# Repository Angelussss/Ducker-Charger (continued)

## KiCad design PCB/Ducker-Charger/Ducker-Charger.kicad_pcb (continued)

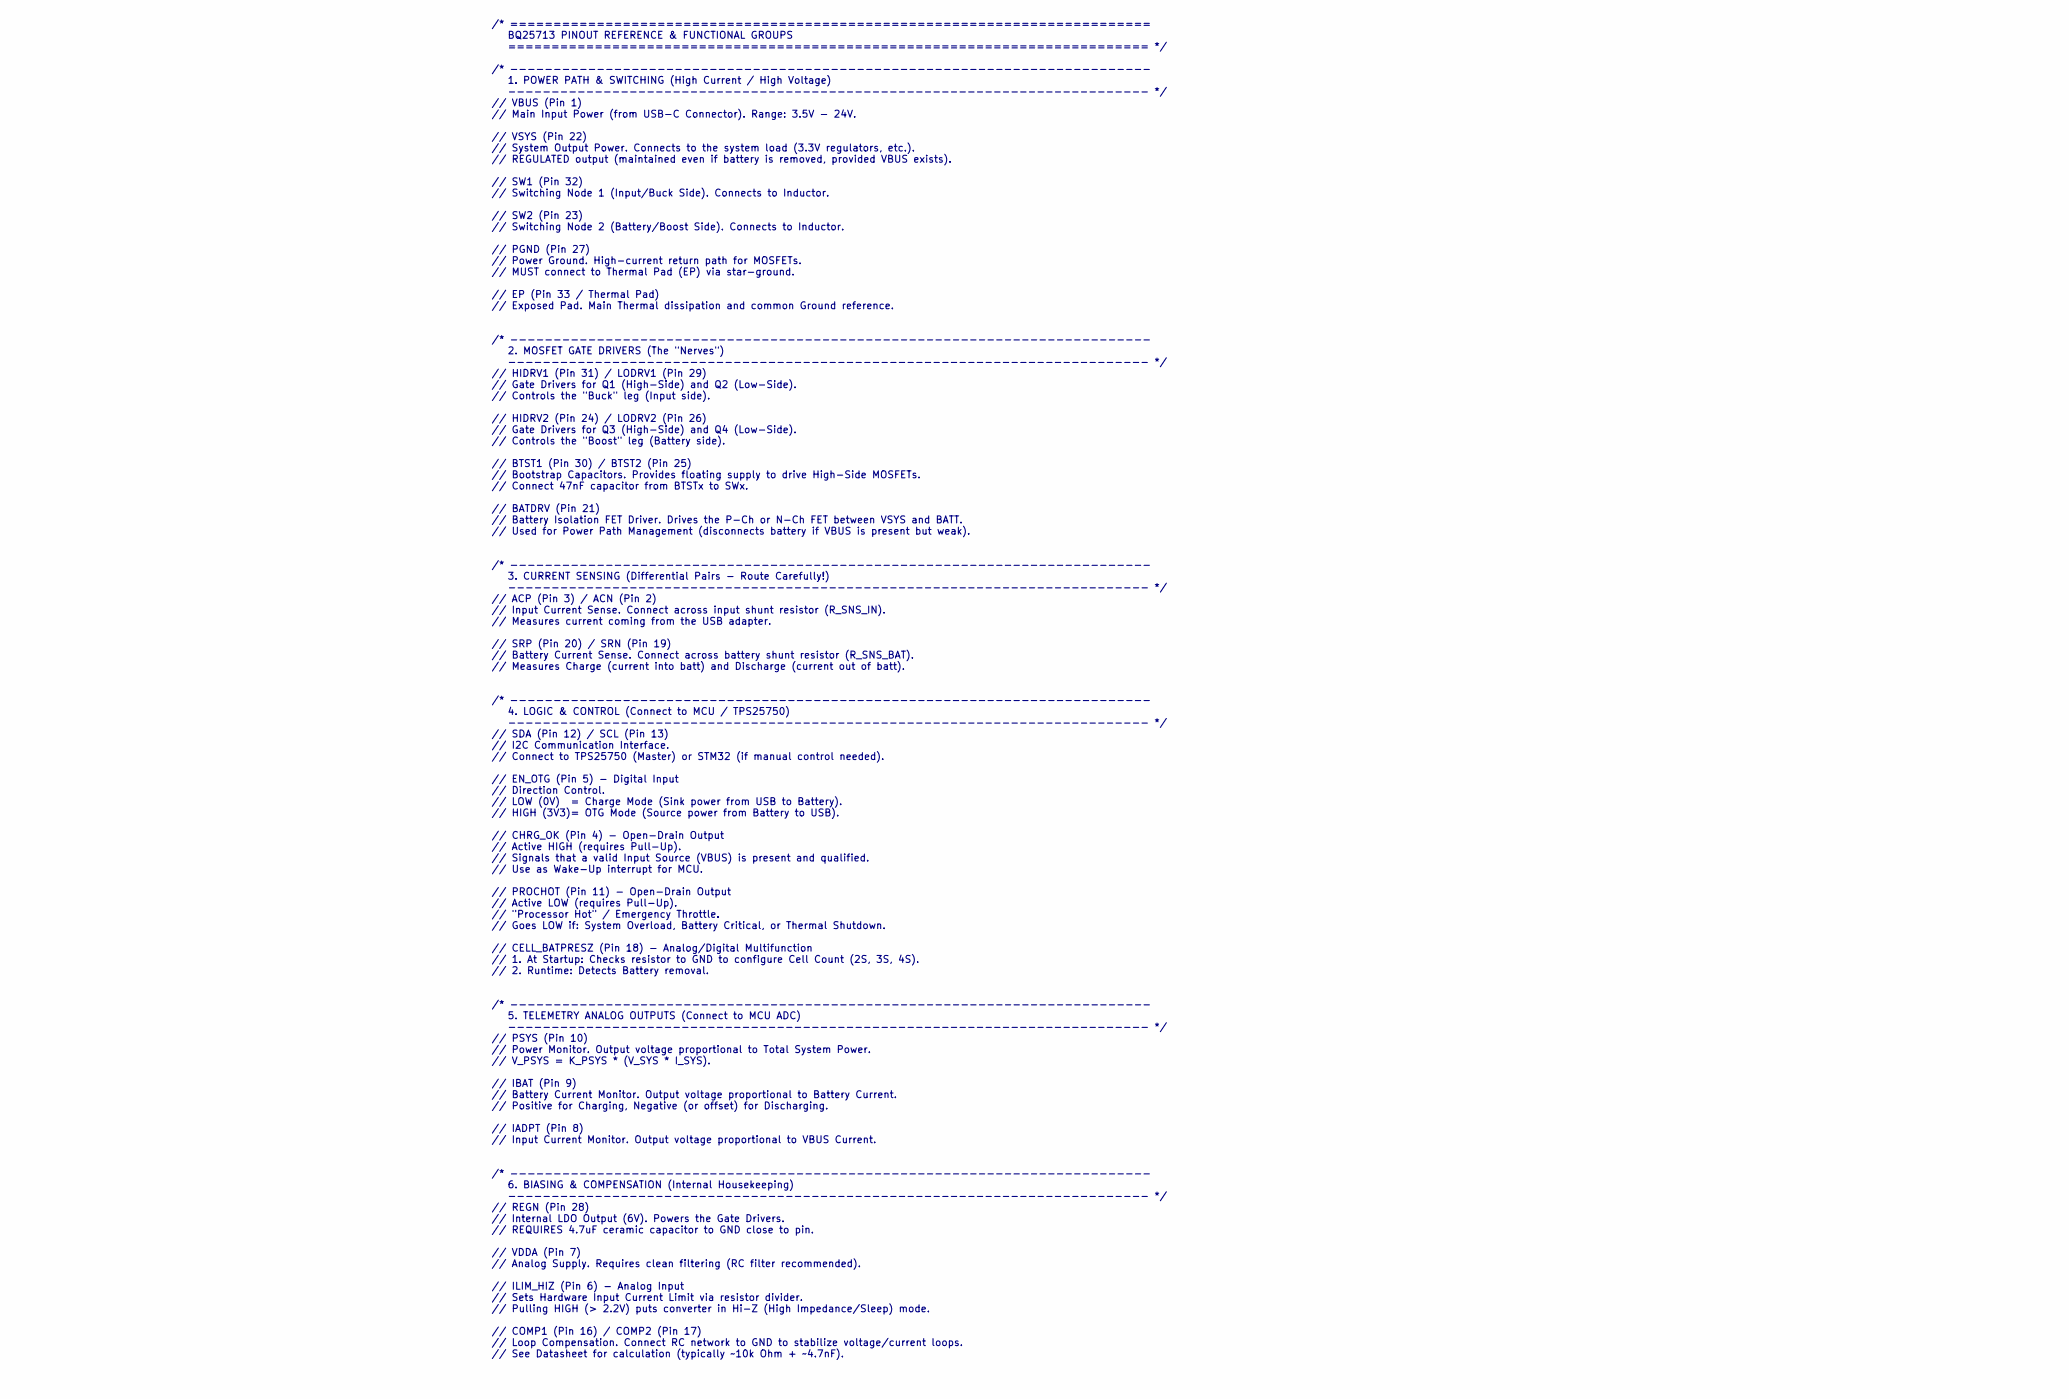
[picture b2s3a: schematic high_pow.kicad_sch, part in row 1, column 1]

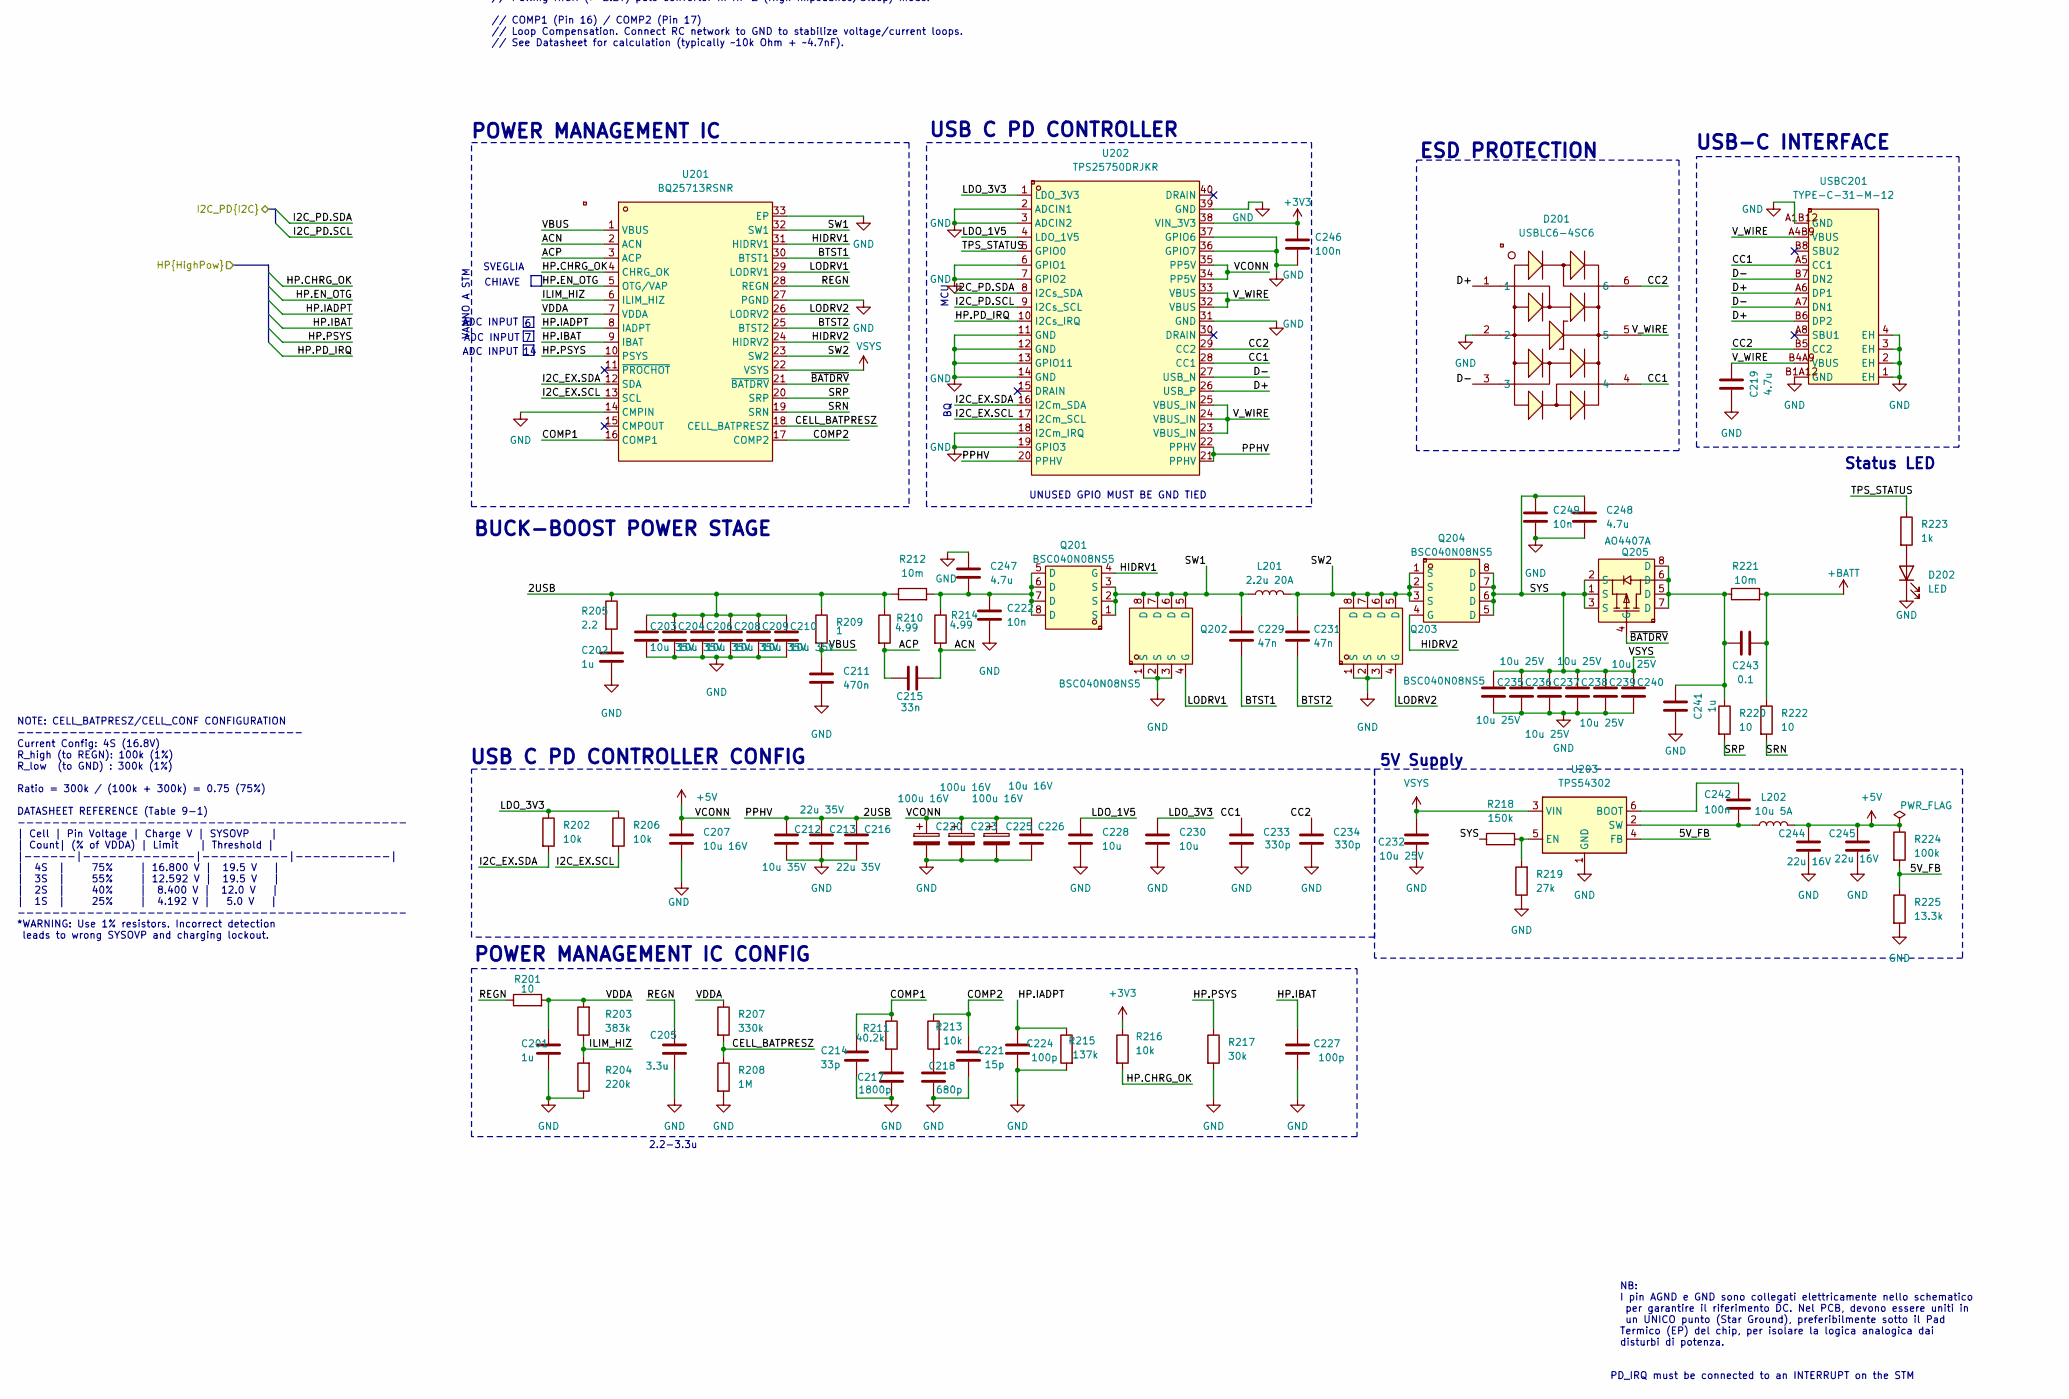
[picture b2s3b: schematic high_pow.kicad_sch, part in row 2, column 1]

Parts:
C201, C202, C241: 1u; C_0805_2012Metric
C203, C204, C206, C208, C209, C210, C212: 10u 35V; C_1206_3216Metric
C205: 3.3u; C_0805_2012Metric
C207, C226: 10u 16V; C_0603_1608Metric
C211: 470n; C_0805_2012Metric
C213, C216: 22u 35V; C_1210_3225Metric
C214: 33p; C_0603_1608Metric
C215: 33n; C_0603_1608Metric
C217: 1800p; C_0603_1608Metric
C218: 680p; C_0603_1608Metric
C219, C247, C248: 4.7u; C_0805_2012Metric
C220, C223, C225: 100u 16V; C_1210_3225Metric
C221: 15p; C_0603_1608Metric
C222, C249: 10n; C_0603_1608Metric
C224, C227: 100p; C_0603_1608Metric
C228, C230: 10u; C_0805_2012Metric
C229, C231: 47n; C_0603_1608Metric
C232, C235, C236, C237, C238, C239, C240: 10u 25V; C_1206_3216Metric
C233, C234: 330p; C_0603_1608Metric
C242, C246: 100n; C_0603_1608Metric
C243: 0.1; C_0805_2012Metric
C244, C245: 22u 16V; C_0805_2012Metric
D201: USBLC6-4SC6; SOT-23-6_L2.9-W1.6-P0.95-LS2.8-BL; LCSC Part C111212
D202: LED; LED_0603_1608Metric
L201: 2.2u 20A; L_Chilisin_BMRF00131360
L202: 10u 5A; L_7.3x7.3_H4.5
Q201, Q202, Q203, Q204: BSC040N08NS5; PG-TDSON-8_L5.9-W5.1-P1.27-LS6.2-BL; LCSC Part C534333
Q205: AO4407A; SOIC-8_L4.9-W3.9-P1.27-LS6.0-BL; LCSC Part C16072
R201, R220, R222: 10; R_0603_1608Metric
R202, R206, R213, R216: 10k; R_0603_1608Metric
R203: 383k; R_0603_1608Metric
R204: 220k; R_0603_1608Metric
R205: 2.2; R_0603_1608Metric
R207: 330k; R_0603_1608Metric
R208: 1M; R_0603_1608Metric
R209: 1; R_0603_1608Metric
R210, R214: 4.99; R_0603_1608Metric
R211: 40.2k; R_0603_1608Metric
R212, R221: 10m; R3920
R215: 137k; R_0603_1608Metric
R217: 30k; R_0603_1608Metric
R218: 150k; R_0603_1608Metric
R219: 27k; R_0603_1608Metric
R223: 1k; R_0603_1608Metric
R224: 100k; R_0603_1608Metric
R225: 13.3k; R_0603_1608Metric
U201: BQ25713RSNR; QFN-32_L4.0-W4.0-P0.40-TL-EP2.8; LCSC Part C2878935
U202: TPS25750DRJKR; QFN-38_L6.0-W4.0-P0.40-TL-EP_RJK; LCSC Part C2868209
U203: TPS54302; SOT-23-6
USBC201: TYPE-C-31-M-12; USB-C_SMD-TYPE-C-31-M-12_1; LCSC Part C165948

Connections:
+3V3: C246.1, R216.1, U202.38 (VIN_3V3); also elsewhere on the board
+5V: C207.1, C220.1, C223.1, C225.1, C226.1, C244.1, C245.1, L202.2, R224.1, U202.34 (PP5V), U202.35 (PP5V); also elsewhere on the board
+BATT: C243.1, R221.2, R222.1; also elsewhere on the board
/High_pow/2USB: C203.1, C204.1, C206.1, C208.1, C209.1, C210.1, C212.1, C213.1, C216.1, R205.1, R209.1, R210.1, R212.1, U202.20 (PPHV), U202.21 (PPHV), U202.22 (PPHV)
/High_pow/5V_FB: R224.2, R225.1, U203.4 (FB)
/High_pow/ACN: C215.2, R214.2, U201.2 (ACN)
/High_pow/ACP: C215.1, R210.2, U201.3 (ACP)
/High_pow/BTST1: C229.2, U201.30 (BTST1)
/High_pow/BTST2: C231.2, U201.25 (BTST2)
/High_pow/CC1: C233.1, D201.4, U202.28 (CC1), USBC201.A5 (CC1)
/High_pow/CC2: C234.1, D201.6, U202.29 (CC2), USBC201.B5 (CC2)
/High_pow/CELL_BATPRESZ: R207.2, R208.1, U201.18 (CELL_BATPRESZ)
/High_pow/COMP1: C214.1, R211.1, U201.16 (COMP1)
/High_pow/COMP2: C221.1, R213.1, U201.17 (COMP2)
/High_pow/D+: D201.1, U202.26 (USB_P), USBC201.A6 (DP1), USBC201.B6 (DP2)
/High_pow/D-: D201.3, U202.27 (USB_N), USBC201.A7 (DN1), USBC201.B7 (DN2)
/High_pow/HIDRV1: Q201.4 (G), U201.31 (HIDRV1)
/High_pow/HIDRV2: Q204.4 (G), U201.24 (HIDRV2)
/High_pow/HP.CHRG_OK: R216.2, U201.4 (CHRG_OK); also elsewhere on the board
/High_pow/HP.EN_OTG: U201.5 (OTG/VAP); also elsewhere on the board
/High_pow/HP.IADPT: C224.1, R215.1, U201.8 (IADPT); also elsewhere on the board
/High_pow/HP.IBAT: C227.1, U201.9 (IBAT); also elsewhere on the board
/High_pow/HP.PD_IRQ: U202.10 (I2Cs_IRQ); also elsewhere on the board
/High_pow/HP.PSYS: R217.1, U201.10 (PSYS); also elsewhere on the board
/High_pow/I2C_EX.SCL: R206.2, U201.13 (SCL), U202.17 (I2Cm_SCL)
/High_pow/I2C_EX.SDA: R202.2, U201.12 (SDA), U202.16 (I2Cm_SDA)
/High_pow/I2C_PD.SCL: U202.9 (I2Cs_SCL); also elsewhere on the board
/High_pow/I2C_PD.SDA: U202.8 (I2Cs_SDA); also elsewhere on the board
/High_pow/ILIM_HIZ: R203.1, R204.2, U201.6 (ILIM_HIZ)
/High_pow/LDO_1V5: C228.1, U202.4 (LDO_1V5)
/High_pow/LDO_3V3: C230.1, R202.1, R206.1, U202.1 (LDO_3V3)
/High_pow/LODRV1: Q202.4 (G), U201.29 (LODRV1)
/High_pow/LODRV2: Q203.4 (G), U201.26 (LODRV2)
/High_pow/REGN: C205.1, R201.1, U201.28 (REGN)
/High_pow/SRN: R222.2, U201.19 (SRN)
/High_pow/SRP: R220.2, U201.20 (SRP)
/High_pow/SW1: C229.1, L201.1, Q201.1 (S), Q201.2 (S), Q201.3 (S), Q202.5 (D), Q202.6 (D), Q202.7 (D), Q202.8 (D), U201.32 (SW1)
/High_pow/SW2: C231.1, L201.2, Q203.5 (D), Q203.6 (D), Q203.7 (D), Q203.8 (D), Q204.1 (S), Q204.2 (S), Q204.3 (S), U201.23 (SW2)
/High_pow/TPS_STATUS: R223.1, U202.5 (GPIO0)
/High_pow/VBUS: C211.1, R209.2, U201.1 (VBUS)
/High_pow/VDDA: C201.1, R201.2, R203.2, R207.1, U201.7 (VDDA)
/High_pow/V_WIRE: C219.1, D201.5, U202.23 (VBUS_IN), U202.24 (VBUS_IN), U202.25 (VBUS_IN), U202.32 (VBUS), U202.33 (VBUS), USBC201.A4B9 (VBUS), USBC201.B4A9 (VBUS)
/High_pow/~BATDRV: Q205.4 (G), U201.21 (~BATDRV)
GND: C201.2, C202.2, C203.2, C204.2, C205.2, C206.2, C207.2, C208.2, C209.2, C210.2, C211.2, C212.2, C213.2, C214.2, C216.2, C217.2, C218.2, C219.2, C220.2, C221.2, C222.2, C223.2, C224.2, C225.2, C226.2, C227.2, C228.2, C230.2, C232.2, C233.2, C234.2, C235.2, C236.2, C237.2, C238.2, C239.2, C240.2, C241.2, C244.2, C245.2, C246.2, C247.1, C248.2, C249.2, D201.2, D202.1 (K), Q202.1 (S), Q202.2 (S), Q202.3 (S), Q203.1 (S), Q203.2 (S), Q203.3 (S), R204.1, R208.2, R215.2, R217.2, R219.1, R225.2, U201.14 (CMPIN), U201.27 (PGND), U201.33 (EP), U202.2 (ADCIN1), U202.3 (ADCIN2), U202.6 (GPIO1), U202.7 (GPIO2), U202.11 (GND), U202.12 (GND), U202.13 (GPIO11), U202.14 (GND), U202.18 (I2Cm_IRQ), U202.19 (GPIO3), U202.31 (GND), U202.36 (GPIO7), U202.37 (GPIO6), U202.39 (GND), U203.1 (GND), USBC201.1 (EH), USBC201.2 (EH), USBC201.3 (EH), USBC201.4 (EH), USBC201.A1B12 (GND), USBC201.B1A12 (GND); also elsewhere on the board
unnamed: C202.1, R205.2
unnamed: C217.1, R211.2
unnamed: C218.1, R213.2
unnamed: C222.1, C247.2, Q201.5 (D), Q201.6 (D), Q201.7 (D), Q201.8 (D), R212.2, R214.1
unnamed: C241.1, C243.2, Q205.5 (D), Q205.6 (D), Q205.7 (D), Q205.8 (D), R220.1, R221.1
unnamed: D202.2 (A), R223.2
unnamed: C242.1, U203.6 (BOOT)
unnamed: R218.2, R219.2, U203.5 (EN)
unnamed: C242.2, L202.1, U203.2 (SW)
VSYS: C232.1, C235.1, C236.1, C237.1, C238.1, C239.1, C240.1, C248.1, C249.1, Q204.5 (D), Q204.6 (D), Q204.7 (D), Q204.8 (D), Q205.1 (S), Q205.2 (S), Q205.3 (S), R218.1, U201.22 (VSYS), U203.3 (VIN); also elsewhere on the board

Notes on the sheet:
BUCK-BOOST POWER STAGE
SVEGLIA
NB: I pin AGND e GND sono collegati elettricamente nello schematico per garantire il riferimento DC. Nel PCB, devono essere uniti in un UNICO punto (Star Ground), preferibilmente sotto il Pad Termico (EP) del chip, per isolare la logica analogica dai disturbi di potenza.
USB C PD CONTROLLER
ESD PROTECTION
PD_IRQ must be connected to an INTERRUPT on the STM
ADC INPUT
POWER MANAGEMENT IC
NOTE: CELL_BATPRESZ/CELL_CONF CONFIGURATION --------------------------------- Current Config: 4S (16.8V) R_high (to REGN): 100k (1%) R_low (to GND) : 300k (1%) Ratio = 300k / (100k + 300k) = 0.75 (75%) DATASHEET REFERENCE (Table 9-1) --------------------------------------------- | Cell | Pin Voltag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
USB C PD CONTROLLER CONFIG
/* ========================================================================== BQ25713 PINOUT REFERENCE & FUNCTIONAL GROUPS ========================================================================== */ /* -------------------------------------------------------------------------- 1. POWER PATH & SWIT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
USB-C INTERFACE
2.2-3.3u
Status LED
5V Supply
VANNO A STM
MCU
POWER MANAGEMENT IC CONFIG
UNUSED GPIO MUST BE GND TIED
CHIAVE

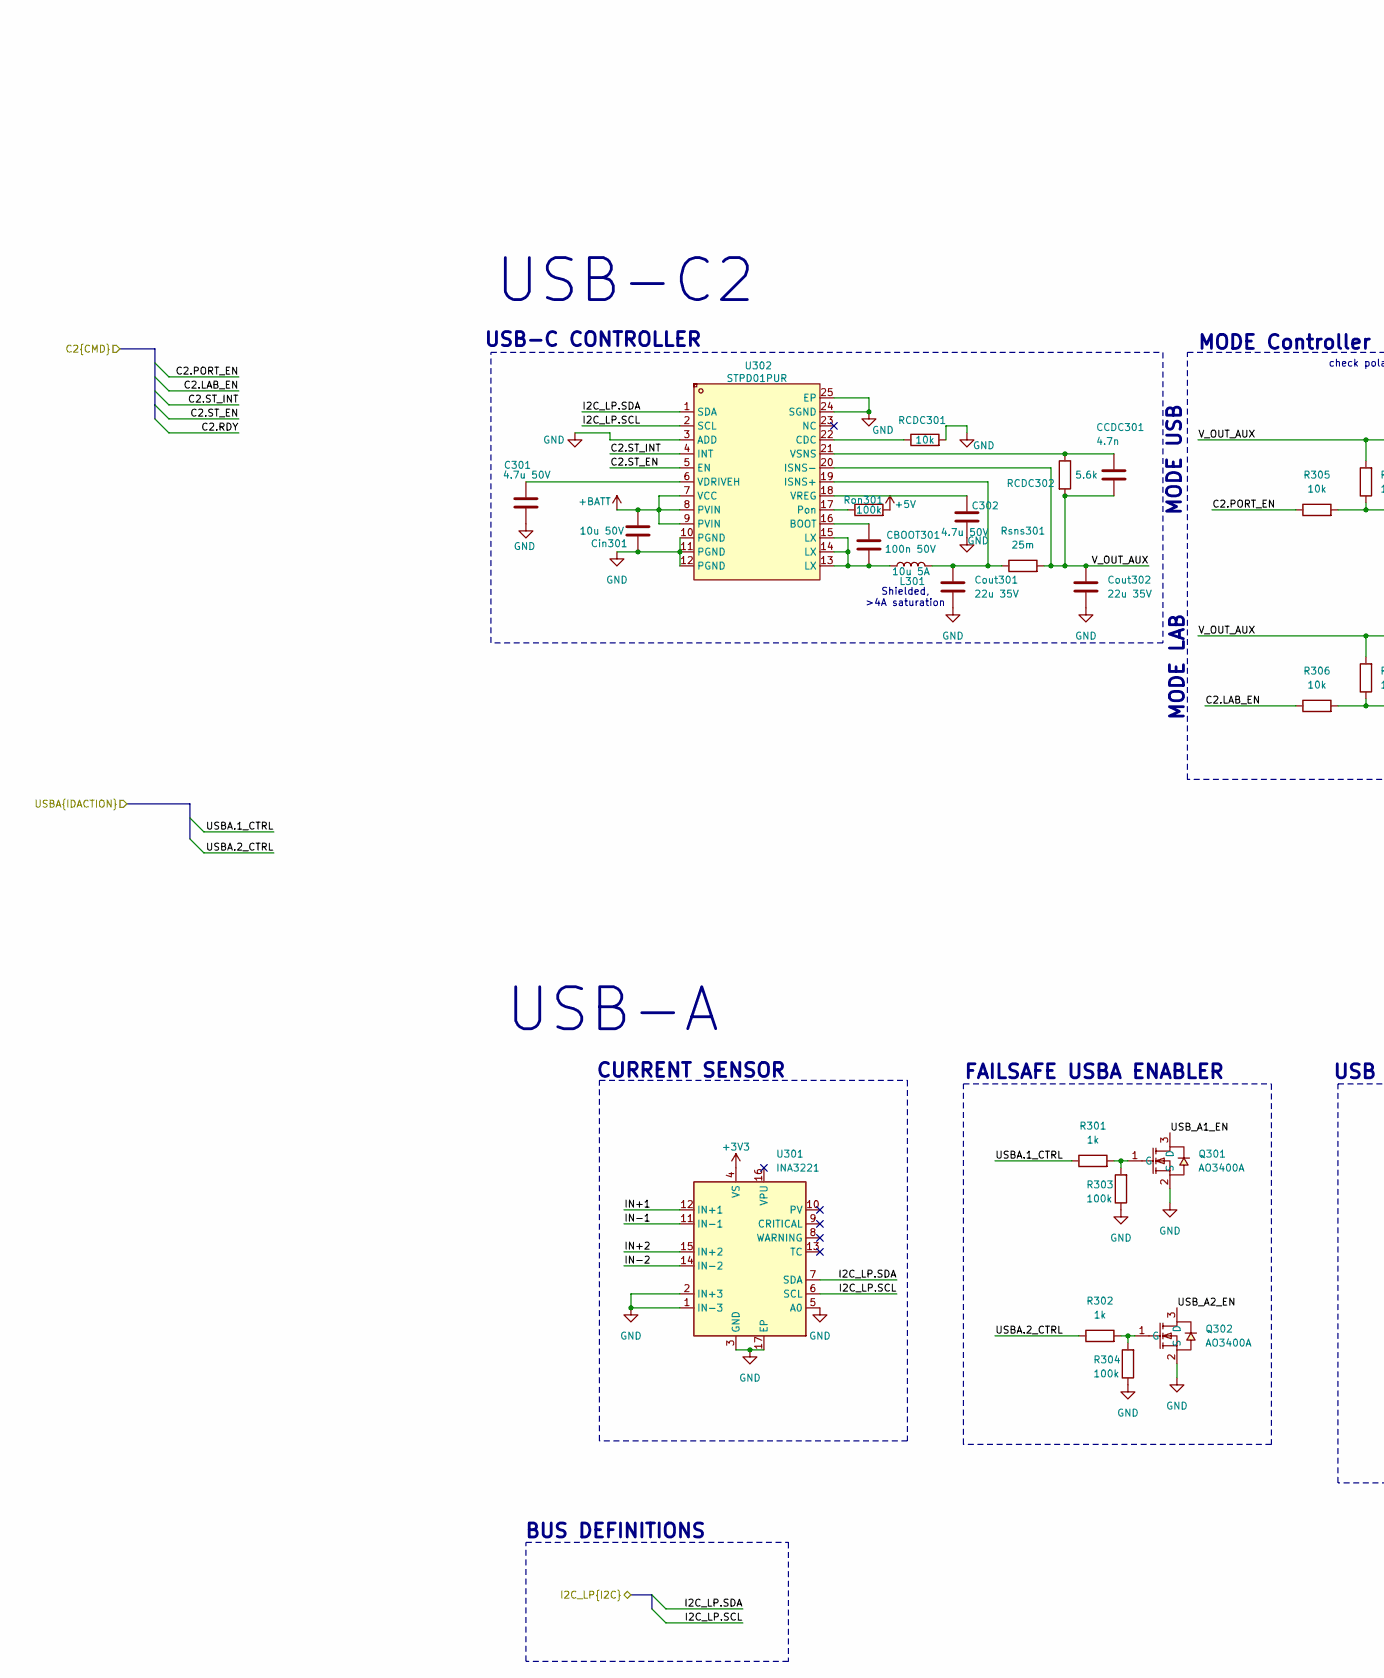
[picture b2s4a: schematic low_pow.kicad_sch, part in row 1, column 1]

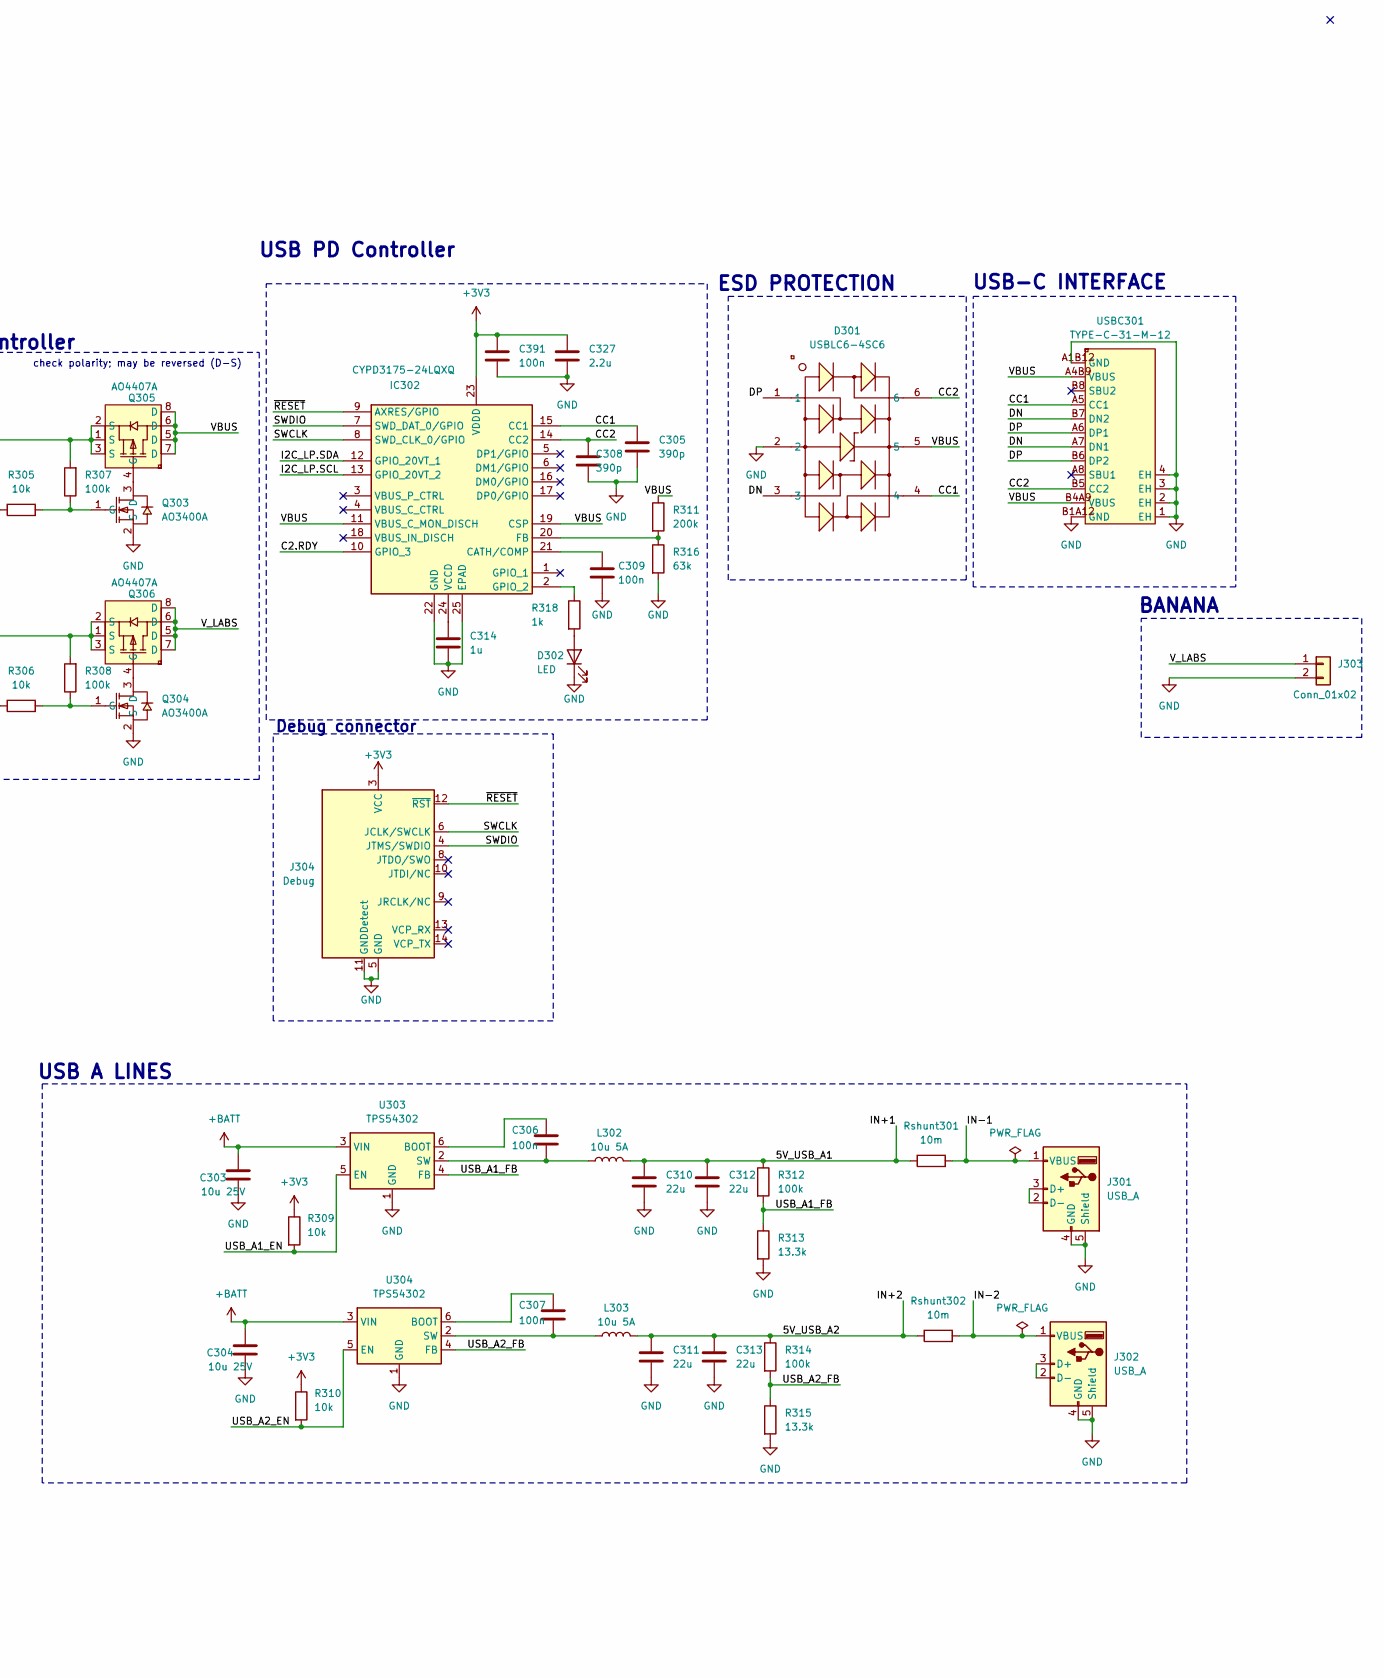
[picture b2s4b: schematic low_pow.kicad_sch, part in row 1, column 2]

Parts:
C301, C302: 4.7u 50V; C_0805_2012Metric
C303, C304: 10u 25V; C_1206_3216Metric
C305, C308: 390p; R_0603_1608Metric
C306, C307: 100n; C_0603_1608Metric
C309, C391: 100n; R_0603_1608Metric
C310, C311, C312, C313: 22u; C_0805_2012Metric
C314: 1u; R_0603_1608Metric
C327: 2.2u; C_0805_2012Metric
CBOOT301: 100n 50V; C_0603_1608Metric
CCDC301: 4.7n; C_0805_2012Metric
Cin301: 10u 50V; C_0805_2012Metric
Cout301, Cout302: 22u 35V; C_1210_3225Metric
D301: USBLC6-4SC6; SOT-23-6_L2.9-W1.6-P0.95-LS2.8-BL; LCSC Part C111212
D302: LED; LED_0603_1608Metric
IC302: CYPD3175-24LQXQ; QFN50P400X400X60-25N-D; Mouser Part Number 727-CYPD3175-24LQXQ
J301, J302: USB_A; USB_A_Molex_67643_Horizontal
J303: Conn_01x02; TerminalBlock_bornier-2_P5.08mm
J304: Debug; SAMTEC_FTSH-107-01-L-DV-K-TR
L301, L302, L303: 10u 5A; L_7.3x7.3_H4.5
Q301, Q302, Q303, Q304: AO3400A; SOT-23-3_L2.9-W1.3-P1.90-LS2.4-BR; LCSC Part C20917
Q305, Q306: AO4407A; SOIC-8_L4.9-W3.9-P1.27-LS6.0-BL; LCSC Part C16072
R301, R302, R318: 1k; R_0603_1608Metric
R303, R304, R307, R308, R312, R314: 100k; R_0603_1608Metric
R305, R306, R309, R310: 10k; R_0603_1608Metric
R311: 200k; R_0603_1608Metric
R313, R315: 13.3k; R_0603_1608Metric
R316: 63k; R_0603_1608Metric
RCDC301: 10k; R_0603_1608Metric
RCDC302: 5.6k; R_0603_1608Metric
Ron301: 100k; R_0603_1608Metric
Rshunt301, Rshunt302: 10m; R_1206_3216Metric
Rsns301: 25m; R_1206_3216Metric
U301: INA3221; Texas_RGV0016A_VQFN-16-1EP_4x4mm_P0.65mm_EP2.1x2.1mm
U302: STPD01PUR; QFN-24_L4.0-W3.0-P0.40-TL-EP; LCSC Part C5268090
U303, U304: TPS54302; SOT-23-6
USBC301: TYPE-C-31-M-12; USB-C_SMD-TYPE-C-31-M-12_1; LCSC Part C165948

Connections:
+3V3: C327.1, C391.1, IC302.23 (VDDD), J304.3 (VCC), R309.1, R310.1, U301.4 (VS); also elsewhere on the board
+5V: Ron301.2; also elsewhere on the board
+BATT: C303.1, C304.1, Cin301.1, U302.7 (VCC), U302.8 (PVIN), U302.9 (PVIN), U303.3 (VIN), U304.3 (VIN); also elsewhere on the board
/BMS/I2C_LP.SCL: IC302.13 (GPIO_20VT_2), U301.6 (SCL), U302.2 (SCL); also elsewhere on the board
/BMS/I2C_LP.SDA: IC302.12 (GPIO_20VT_1), U301.7 (SDA), U302.1 (SDA); also elsewhere on the board
/Logic/C2.LAB_EN: R306.1; also elsewhere on the board
/Logic/C2.PORT_EN: R305.1; also elsewhere on the board
/Logic/C2.RDY: IC302.10 (GPIO_3); also elsewhere on the board
/Logic/C2.ST_EN: U302.5 (EN); also elsewhere on the board
/Logic/C2.ST_INT: U302.4 (INT); also elsewhere on the board
/Logic/USBA.1_CTRL: R301.1; also elsewhere on the board
/Logic/USBA.2_CTRL: R302.1; also elsewhere on the board
/Low_pow/5V_USB_A1: C310.1, C312.1, L302.2, R312.1, Rshunt301.1, U301.12 (IN+1)
/Low_pow/5V_USB_A2: C311.1, C313.1, L303.2, R314.1, Rshunt302.1, U301.15 (IN+2)
/Low_pow/CC1: C305.1, D301.4, IC302.15 (CC1), USBC301.A5 (CC1)
/Low_pow/CC2: C308.1, D301.6, IC302.14 (CC2), USBC301.B5 (CC2)
/Low_pow/DN: D301.3, USBC301.A7 (DN1), USBC301.B7 (DN2)
/Low_pow/DP: D301.1, USBC301.A6 (DP1), USBC301.B6 (DP2)
/Low_pow/IN-1: J301.1 (VBUS), Rshunt301.2, U301.11 (IN-1)
/Low_pow/IN-2: J302.1 (VBUS), Rshunt302.2, U301.14 (IN-2)
/Low_pow/SWCLK: IC302.8 (SWD_CLK_0/GPIO), J304.6 (JCLK/SWCLK)
/Low_pow/SWDIO: IC302.7 (SWD_DAT_0/GPIO), J304.4 (JTMS/SWDIO)
/Low_pow/USB_A1_EN: Q301.3 (D), R309.2, U303.5 (EN)
/Low_pow/USB_A1_FB: R312.2, R313.1, U303.4 (FB)
/Low_pow/USB_A2_EN: Q302.3 (D), R310.2, U304.5 (EN)
/Low_pow/USB_A2_FB: R314.2, R315.1, U304.4 (FB)
/Low_pow/VBUS: D301.5, IC302.11 (VBUS_C_MON_DISCH), IC302.19 (CSP), Q305.5 (D), Q305.6 (D), Q305.7 (D), Q305.8 (D), R311.1, USBC301.A4B9 (VBUS), USBC301.B4A9 (VBUS)
/Low_pow/V_LABS: J303.1, Q306.5 (D), Q306.6 (D), Q306.7 (D), Q306.8 (D)
/Low_pow/V_OUT_AUX: CCDC301.2, Cout302.1, Q305.1 (S), Q305.2 (S), Q305.3 (S), Q306.1 (S), Q306.2 (S), Q306.3 (S), R307.2, R308.2, RCDC302.2, Rsns301.2, U302.20 (ISNS-)
/Low_pow/~RESET: IC302.9 (AXRES/GPIO), J304.12 (~RST)
GND: C301.2, C302.2, C303.2, C304.2, C305.2, C308.2, C309.2, C310.2, C311.2, C312.2, C313.2, C314.2, C327.2, C391.2, Cin301.2, Cout301.2, Cout302.2, D301.2, D302.1 (K), IC302.22 (GND), IC302.25 (EPAD), J301.4 (GND), J301.5 (Shield), J302.4 (GND), J302.5 (Shield), J303.2, J304.5 (GND), J304.7 (GND), J304.11 (GNDDetect), Q301.2 (S), Q302.2 (S), Q303.2 (S), Q304.2 (S), R303.1, R304.1, R313.2, R315.2, R316.2, RCDC301.2, U301.1 (IN-3), U301.2 (IN+3), U301.3 (GND), U301.5 (A0), U301.17 (EP), U302.3 (ADD), U302.10 (PGND), U302.11 (PGND), U302.12 (PGND), U302.24 (SGND), U302.25 (EP), U303.1 (GND), U304.1 (GND), USBC301.1 (EH), USBC301.2 (EH), USBC301.3 (EH), USBC301.4 (EH), USBC301.A1B12 (GND), USBC301.B1A12 (GND); also elsewhere on the board
unnamed: CBOOT301.2, L301.1, U302.13 (LX), U302.14 (LX), U302.15 (LX)
unnamed: D302.2 (A), R318.2
unnamed: C309.1, IC302.21 (CATH/COMP)
unnamed: IC302.20 (FB), R311.2, R316.1
unnamed: IC302.2 (GPIO_2), R318.1
unnamed: C314.1, IC302.24 (VCCD)
unnamed: J301.2 (D-), J301.3 (D+)
unnamed: J302.2 (D-), J302.3 (D+)
unnamed: Q301.1 (G), R301.2, R303.2
unnamed: Q302.1 (G), R302.2, R304.2
unnamed: Q303.3 (D), Q305.4 (G)
unnamed: Q303.1 (G), R305.2, R307.1
unnamed: Q304.3 (D), Q306.4 (G)
unnamed: Q304.1 (G), R306.2, R308.1
unnamed: CBOOT301.1, U302.16 (BOOT)
unnamed: RCDC301.1, U302.22 (CDC)
unnamed: Cout301.1, L301.2, Rsns301.1, U302.19 (ISNS+)
unnamed: Ron301.1, U302.17 (Pon)
unnamed: C301.1, U302.6 (VDRIVEH)
unnamed: C302.1, U302.18 (VREG)
unnamed: CCDC301.1, RCDC302.1, U302.21 (VSNS)
unnamed: C306.1, U303.6 (BOOT)
unnamed: C306.2, L302.1, U303.2 (SW)
unnamed: C307.1, U304.6 (BOOT)
unnamed: C307.2, L303.1, U304.2 (SW)

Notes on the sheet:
BUS DEFINITIONS
USB-C CONTROLLER
USB-C2
Shielded, >4A saturation
USB-C INTERFACE
USB PD Controller
FAILSAFE USBA ENABLER
CURRENT SENSOR
MODE USB
Debug connector
USB-A
MODE Controller
USB A LINES
ESD PROTECTION
BANANA
MODE LAB
check polarity; may be reversed (D-S)

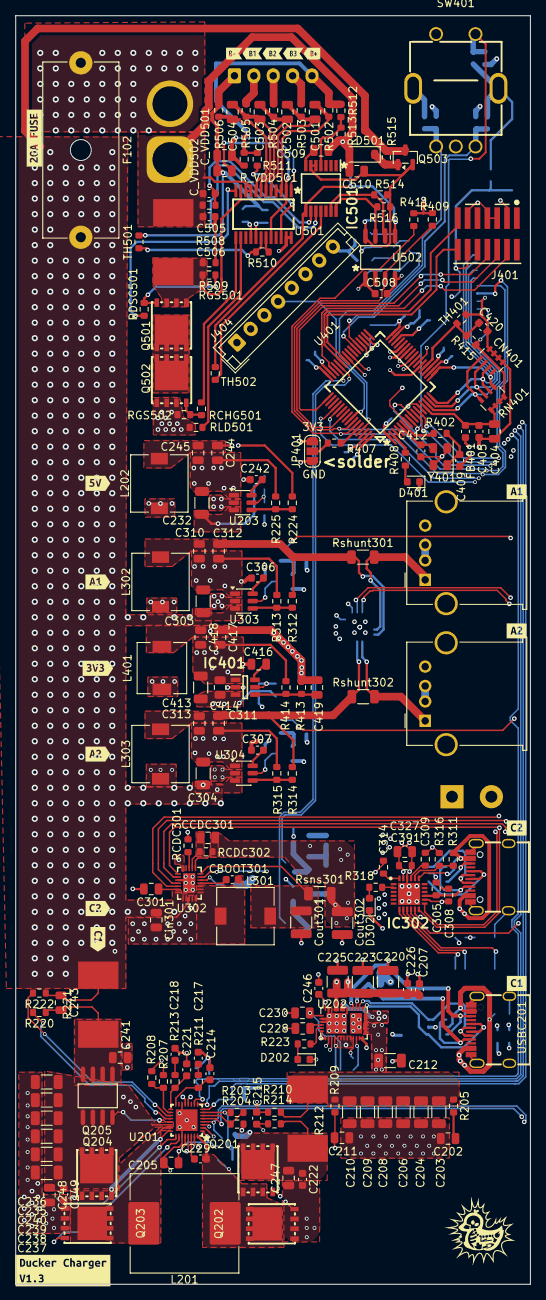
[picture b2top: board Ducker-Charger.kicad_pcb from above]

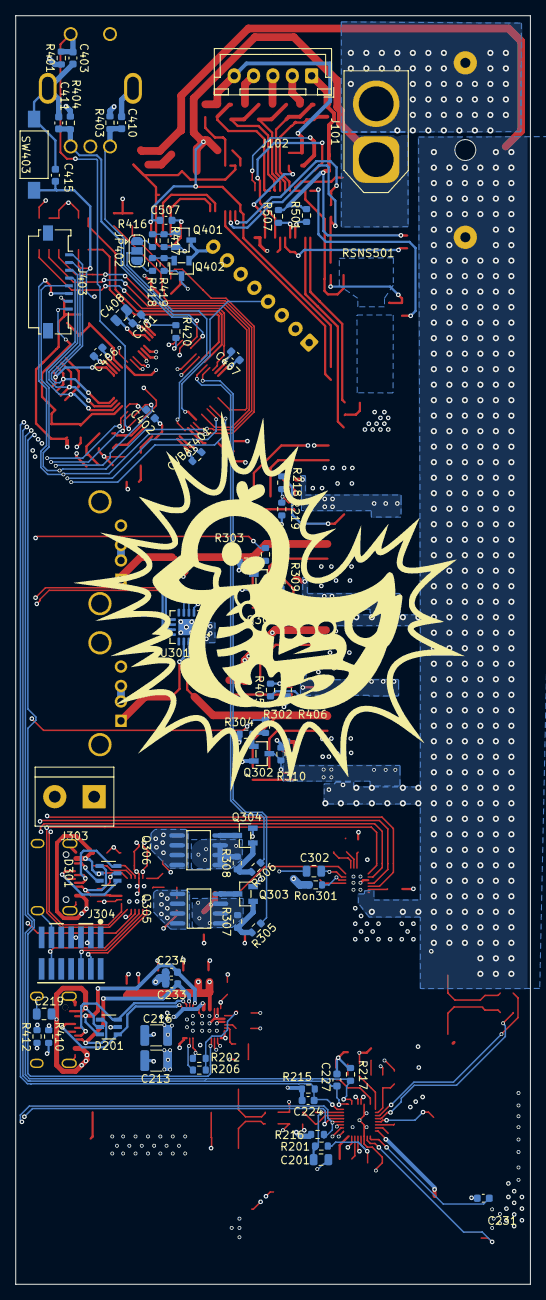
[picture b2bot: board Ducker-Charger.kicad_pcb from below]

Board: 4 copper layers, 66.4 x 163.6 mm, 276 parts (72 on the bottom side), 180 nets.

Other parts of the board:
F102: 20A; Fuseholder_Cylinder-5x20mm_Schurter_0031_8201_Horizontal_Op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
J101: Conn_01x02; AMASS_XT60-M_1x02_P7.20mm_Vertical
J102: Conn_01x05; JST_XH_B5B-XH-A_1x05_P2.50mm_Vertical
kibuzzard-6A3BBBB4: G***; kibuzzard-6A3BBBB4
kibuzzard-6A3BBBD7: G***; kibuzzard-6A3BBBD7
kibuzzard-6A3BBBE2: G***; kibuzzard-6A3BBBE2
kibuzzard-6A3BBBEB: G***; kibuzzard-6A3BBBEB
kibuzzard-6A3BBBFC: G***; kibuzzard-6A3BBBFC
kibuzzard-6A3BBC07: G***; kibuzzard-6A3BBC07
kibuzzard-6A3BBC42: G***; kibuzzard-6A3BBC42
kibuzzard-6A3BBDB6: G***; kibuzzard-6A3BBDB6
kibuzzard-6A3BBDBF: G***; kibuzzard-6A3BBDBF
kibuzzard-6A3BBDD0: G***; kibuzzard-6A3BBDD0
kibuzzard-6A3BBDD9: G***; kibuzzard-6A3BBDD9
kibuzzard-6A3C421F: G***; kibuzzard-6A3C421F
kibuzzard-694FF1FC: G***; kibuzzard-694FF1FC
kibuzzard-694FF21A: G***; kibuzzard-694FF21A
kibuzzard-694FF228: G***; kibuzzard-694FF228
kibuzzard-694FF236: G***; kibuzzard-694FF236
kibuzzard-694FF248: G***; kibuzzard-694FF248

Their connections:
+BATT: F102.2; also elsewhere on the board
-BATT: J101.1; also elsewhere on the board
BATT_SENS_B1: J102.2; also elsewhere on the board
BATT_SENS_B2: J102.3; also elsewhere on the board
BATT_SENS_B3: J102.4; also elsewhere on the board
BATT_SENS_B+: J102.5; also elsewhere on the board
BATT_SENS_B-: J102.1; also elsewhere on the board
unnamed: F102.1, J101.2

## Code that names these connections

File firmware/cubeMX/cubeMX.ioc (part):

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Mcu.Name=STM32F401R(B-C)Tx
Mcu.Package=LQFP64
Mcu.UserName=STM32F401RBTx
PA0-WKUP.Signal=ADCx_IN0
PA1.Signal=ADCx_IN1
PA10.Mode=Asynchronous
PA10.Signal=USART1_RX
PA11.GPIOParameters=GPIO_Label
PA11.GPIO_Label=C2_LAB_EN
PA11.Signal=GPIO_Output
PA12.GPIOParameters=GPIO_Label
PA12.GPIO_Label=C2_PORT_EN
PA12.Signal=GPIO_Output
PA13.Mode=Trace_Asynchronous_SW
PA13.Signal=SYS_JTMS-SWDIO
PA14.Mode=Trace_Asynchronous_SW
PA14.Signal=SYS_JTCK-SWCLK
PA2.Signal=ADCx_IN2
PA3.Signal=ADCx_IN3
PA4.Signal=ADCx_IN4
PA5.Mode=TX_Only_Simplex_Unidirect_Master
PA5.Signal=SPI1_SCK
PA6.Signal=ADCx_IN6
PA7.Signal=ADCx_IN7
PA8.Mode=I2C
PA8.Signal=I2C3_SCL
PA9.Mode=Asynchronous
PA9.Signal=USART1_TX
PB0.GPIOParameters=GPIO_Speed,PinState,GPIO_Label
PB0.GPIO_Label=DISP_CS
PB0.GPIO_Speed=GPIO_SPEED_FREQ_VERY_HIGH
PB0.PinState=GPIO_PIN_SET
PB0.Signal=GPIO_Output
PB1.GPIOParameters=GPIO_Speed,GPIO_Label
PB1.GPIO_Label=DISP_DC
PB1.GPIO_Speed=GPIO_SPEED_FREQ_VERY_HIGH
PB1.Signal=GPIO_Output
PB13.GPIOParameters=GPIO_Label
PB13.GPIO_Label=HP_CHRG_OK
PB13.Signal=GPIO_Input
PB14.GPIOParameters=GPIO_Label
PB14.GPIO_Label=HP_PD_IRQ
PB14.Signal=GPIO_Input
PB15.GPIOParameters=GPIO_Label
PB15.GPIO_Label=HP_EN_OTG
PB15.Signal=GPIO_Output
PB2.GPIOParameters=PinState,GPIO_Label
PB2.GPIO_Label=DISP_RST
PB2.PinState=GPIO_PIN_SET
PB2.Signal=GPIO_Output
PB3.Mode=Trace_Asynchronous_SW
PB3.Signal=SYS_JTDO-SWO
PB5.Mode=TX_Only_Simplex_Unidirect_Master
PB5.Signal=SPI1_MOSI
PB6.Mode=I2C
PB6.Signal=I2C1_SCL
PB7.Mode=I2C
PB7.Signal=I2C1_SDA
PB8.GPIOParameters=GPIO_Label
PB8.GPIO_Label=BCKL_CTRL
PB8.Signal=GPIO_Output
PC0.GPIOParameters=GPIO_Label
PC0.GPIO_Label=ENCOD_BUTT
PC0.Signal=GPIO_Input
PC1.GPIOParameters=GPIO_Label
PC1.GPIO_Label=USB_A1_CTRL
PC1.Signal=GPIO_Output
PC11.GPIOParameters=GPIO_Label
PC11.GPIO_Label=C2_ST_EN
PC11.Signal=GPIO_Output
PC12.GPIOParameters=GPIO_Label
PC12.GPIO_Label=C2_ST_INT
PC12.Signal=GPIO_Input
PC13-ANTI_TAMP.GPIOParameters=PinState,GPIO_Label
PC13-ANTI_TAMP.GPIO_Label=STATUS
PC13-ANTI_TAMP.PinState=GPIO_PIN_SET
PC13-ANTI_TAMP.Signal=GPIO_Output
PC2.GPIOParameters=GPIO_Label
PC2.GPIO_Label=USB_A2_CTRL
PC2.Signal=GPIO_Output
PC3.GPIOParameters=GPIO_Label
PC3.GPIO_Label=C2_RDY
PC3.Signal=GPIO_Input
PC4.Signal=ADCx_IN14
PC6.Signal=S_TIM3_CH1
PC7.Signal=S_TIM3_CH2
PC9.Mode=I2C
PC9.Signal=I2C3_SDA
PH0\ -\ OSC_IN.Mode=HSE-External-Oscillator
PH0\ -\ OSC_IN.Signal=RCC_OSC_IN
PH1\ -\ OSC_OUT.Mode=HSE-External-Oscillator
PH1\ -\ OSC_OUT.Signal=RCC_OSC_OUT
RCC.HSE_VALUE=16000000
RCC.SYSCLKFreq_VALUE=84000000
RCC.SYSCLKSource=RCC_SYSCLKSOURCE_PLLCLK
board=custom

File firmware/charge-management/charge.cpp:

#include "charge.h"
#include "../cubeMX/Drivers/STM32F4xx_HAL_Driver/Inc/stm32f4xx_hal_adc.h"
#include <iostream>

using namespace std;

const float MAX_V = 16.8;
const float NOMINAL_V = 14.4;

const float DEFAULT_VOLTAGE = 0.0;      // To be defined

/*  Read via ADC1; VREF+ = VDD (+3.3V)
    Signal Name     STM32 Pin	ADC Channel	Description
    ----------------------------------------------------------------------
    NTC_1	        PA0	        IN0	            Temp Zone 1 (General/FETs)
    ----------------------------------------------------------------------
    NTC_2	        PA1	        IN1	            Temp Zone 2
    ----------------------------------------------------------------------
    NTC_3	        PA2	        IN2	            Temp Zone 3
    ----------------------------------------------------------------------
    NTC_4	        PA3	        IN3	            Temp Zone 4
    ----------------------------------------------------------------------
    HP.IADPT	    PA6	        IN6	            USB-C Input Current
    ----------------------------------------------------------------------
    HP.IBAT	        PA7	        IN7	            Battery Current (Charge/Discharge)
    ----------------------------------------------------------------------
    HP.PSYS	        PC4	        IN14	        Total System Power
*/

/*  ADC:
*** Polling mode IO operation ***
     =================================
     [..]
       (+) Start the ADC peripheral using HAL_ADC_Start()
       (+) Wait for end of conversion using HAL_ADC_PollForConversion(), at this stage
           user can specify the value of timeout according to his end application
       (+) To read the ADC converted values, use the HAL_ADC_GetValue() function.
       (+) Stop the ADC peripheral using HAL_ADC_Stop()
*/

void readSensors() {
    ADC_HandleTypeDef hadc;
    // Start the ADC peripheral
    HAL_ADC_Start(&hadc);

    // Read Temp Zone 1


    // Stop the ADC peripheral
    HAL_ADC_Stop(&hadc);

}

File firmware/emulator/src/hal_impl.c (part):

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/* output-pin names for the log (indexed lookup, else generic) */
static const char *pin_name(int port, int pinno)
{
    if (port == 2 && pinno == 1)  return "USB_A1_EN";
    if (port == 2 && pinno == 2)  return "USB_A2_EN";
    if (port == 2 && pinno == 11) return "STPD01_EN";
    if (port == 0 && pinno == 12) return "USB_C2_EN";
    if (port == 0 && pinno == 11) return "C2_LAB_EN";
    if (port == 1 && pinno == 15) return "EN_OTG";
    if (port == 1 && pinno == 8)  return "BCKL_CTRL";
    return NULL;
}

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HAL_StatusTypeDef HAL_TIM_Encoder_Start(TIM_HandleTypeDef *h, uint32_t ch)
{ (void)h; (void)ch; return HAL_OK; }

/* TIM10_CH1 drives BCKL_CTRL (PB8). The panel only needs a level, so PWM
 * collapses to "duty > 0 = active level", polarity from the firmware's
 * own OC config. Logged so brightness changes are visible headless. */
TIM_TypeDef sim_tim10_regs;
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     * CHRG_OK is the BQ25713 power-good output: LOW until a valid
     * adapter is present, faithful even though it means charge.c
     * pushes EVT_ERROR on the very first readCS(). */
    sim_gpio_drive_input(1, 14, 1);  /* PB14 PD_IRQ        */
    sim_gpio_drive_input(2, 12, 1);  /* PC12 STPD01_INT    */
    sim_gpio_drive_input(2, 3,  1);  /* PC3  CYPD3175_INT  */
    sim_gpio_drive_input(1, 13, board.charger_attached ? 1 : 0);
    sim_gpio_drive_input(2, 0,  1);  /* PC0  encoder button (active low) */
}

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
